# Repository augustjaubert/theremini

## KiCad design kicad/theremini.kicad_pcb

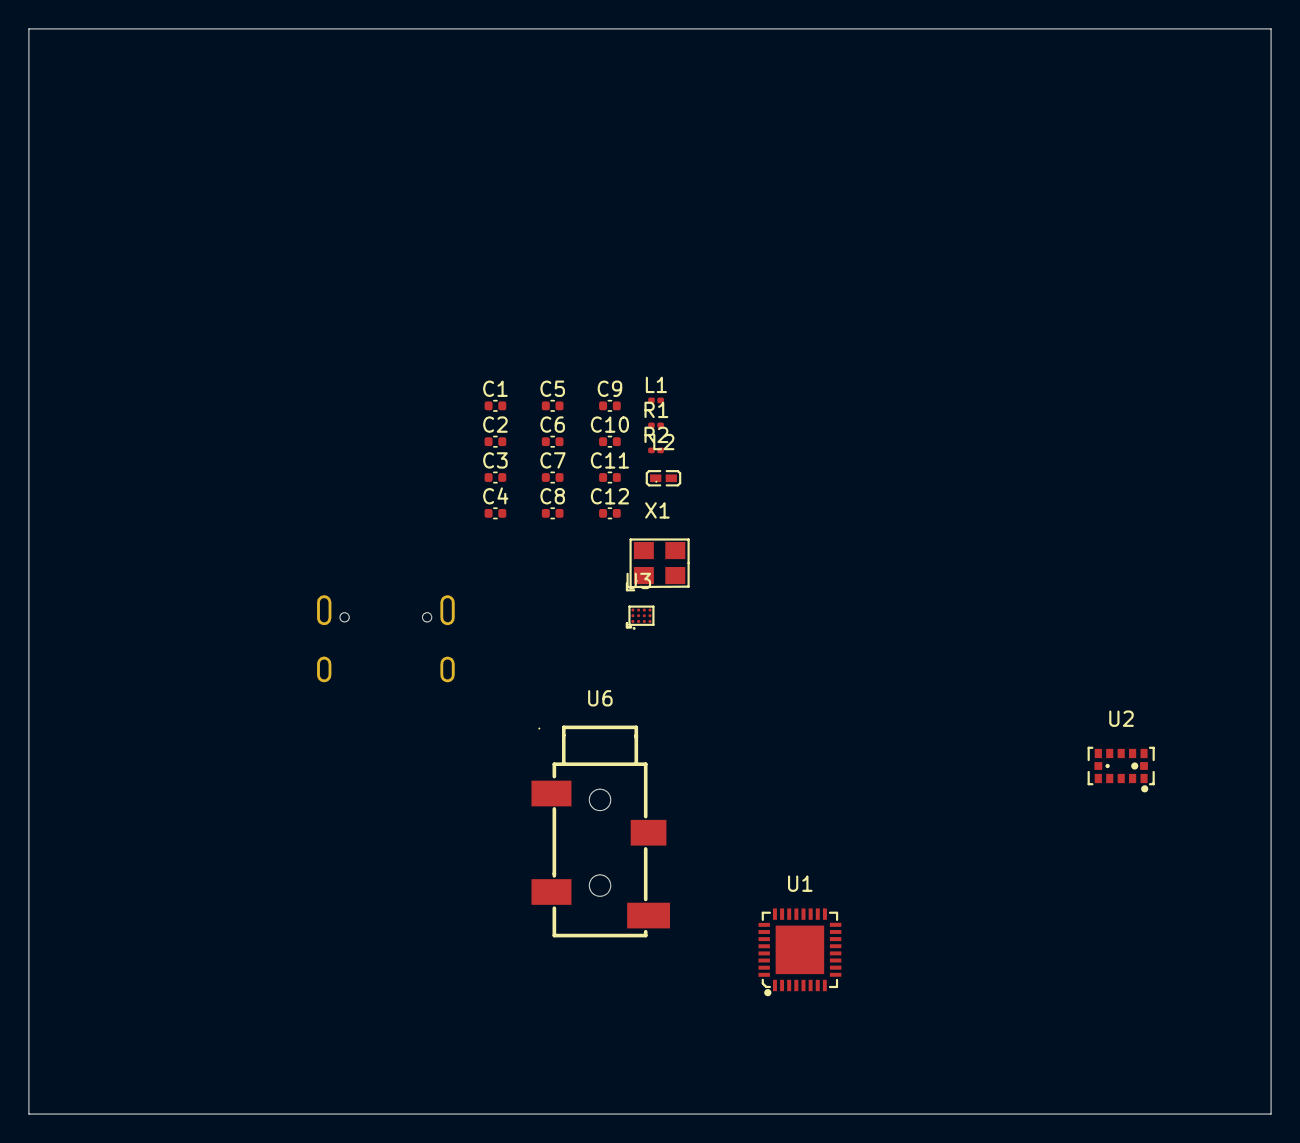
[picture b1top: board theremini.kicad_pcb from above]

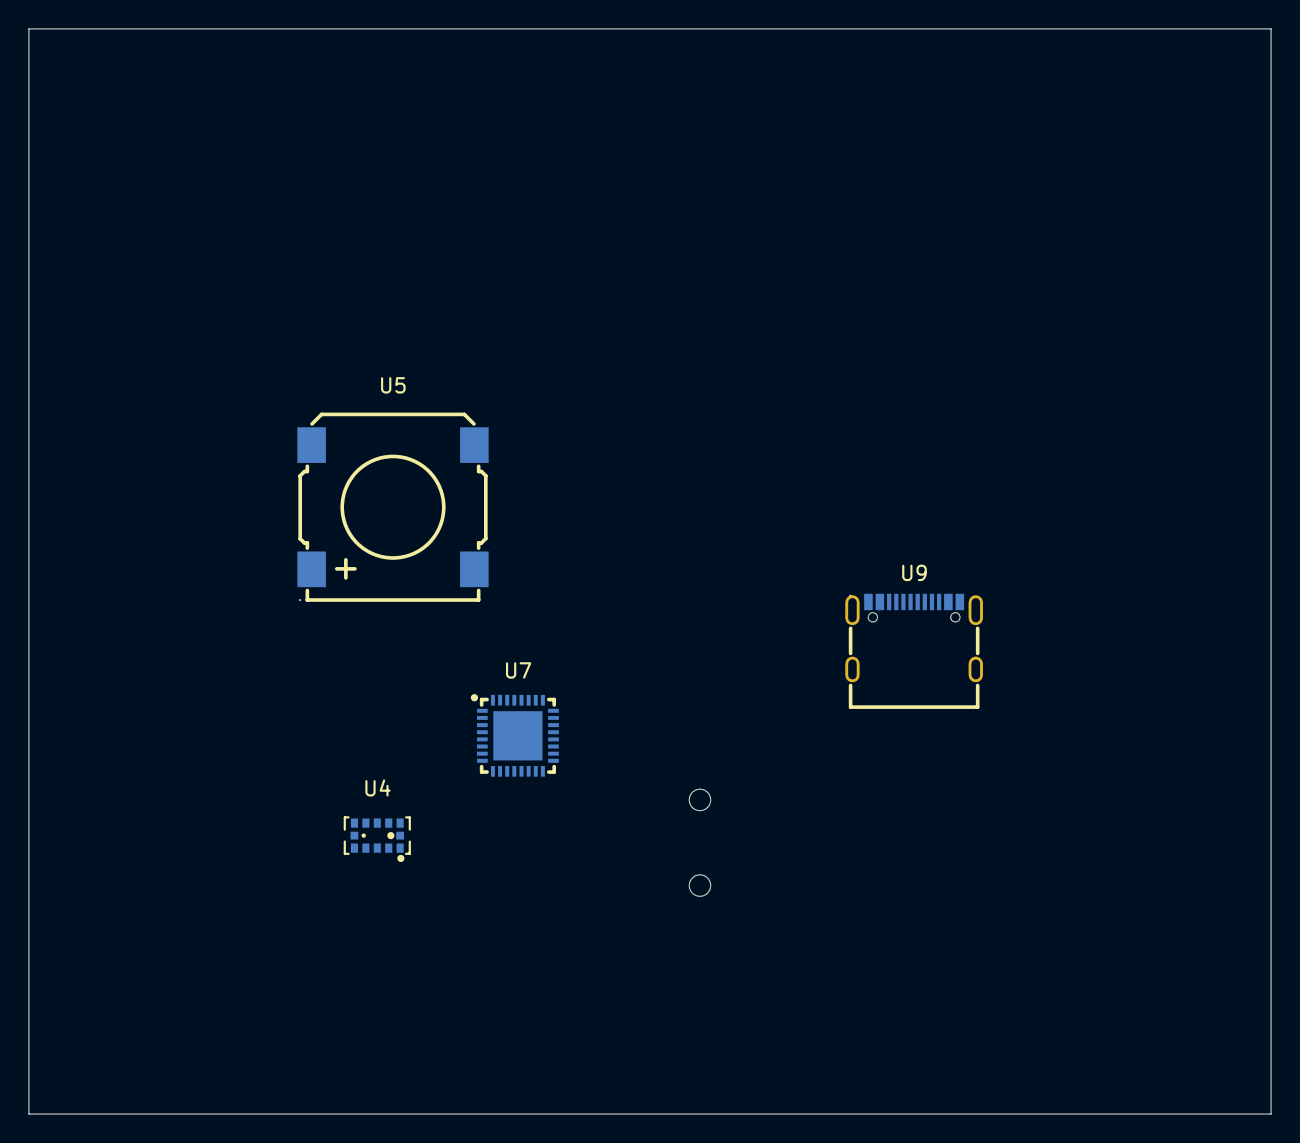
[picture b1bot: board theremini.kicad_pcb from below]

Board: 2 copper layers, 87.0 x 76.0 mm, 25 parts (4 on the bottom side), 12 nets, no tracks yet.

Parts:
C1, C2, C3: 10u; C_0402_1005Metric
C4: 1n; C_0402_1005Metric
C5: 4u7; C_0402_1005Metric
C6, C7, C10, C11: 100n; C_0402_1005Metric
C8: 10n; C_0402_1005Metric
C9: 1u; C_0402_1005Metric
C12: 15p; C_0402_1005Metric
L1: 1.5u; L_0201_0603Metric
L2: BLM15AG601SN1D; L0402
R1: 1M; R_0201_0603Metric
R2: 10k; R_0201_0603Metric
U1: NAU88C22YG; QFN-32_L5.0-W5.0-P0.50-BL-EP3.4
U2, U4: VL53L0CXV0DH/1; OPTO-SMD_12P_VL53L0CXV0DH-1
U3: TPS63051YFFR; DSBGA-12_L1.6-W1.2-R3-C4-P0.40-BL
U5: KLJ-01304T-08R07W; BUZ-SMD_4P-L13.0-W13.0-P11.4-BL
U6: PJ-327C-4A; AUDIO-SMD_PJ-327C-4A
U7: STM32L432KBU6TR; UFQFPN-32_L5.0-W5.0-P0.50-TL-EP3.5
U9: TYPE-C16PIN; USB-C-SMD_TYPE-C16PIN
X1: OT32258MJBA4SL; OSC-SMD_4P-L3.2-W2.5-BL

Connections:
+3.3V: C2.2, C3.2, C5.1, C6.1, C7.1, C11.1, L2.1, R1.2, U3.D1 (VOUT), U3.D2 (FB), U7.1 (VDD), U7.17 (VDD), X1.1 (Tri-state), X1.4 (VDD)
BUCK CONVERTER IN: C1.1, U3.A2 (VIN), U3.A3 (EN), U3.B2 (ILIM0), U3.B3 (ILIM1)
GND: C1.2, C2.1, C3.1, C4.1, C5.2, C6.2, C7.2, C8.2, C9.2, C10.2, C11.2, C12.2, R2.1, U3.B1 (GND), U3.C2 (PFM/PWM), U7.32 (VSS), U9.1 (SHELL), U9.2 (SHELL), U9.3 (SHELL), U9.4 (SHELL), U9.A1B12 (GND), U9.B1A12 (GND), X1.2 (GND)
NRST: C10.1, U7.4 (NRST)
unnamed: U9.A4B9 (VBUS), U9.B4A9 (VBUS)
unnamed: L1.1, U3.A1 (L1)
unnamed: L1.2, U3.C1 (L2)
unnamed: R1.1, U3.C3 (PG)
unnamed: C4.2, U3.D3 (SS)
unnamed: R2.2, U7.31 (PH3/BOOT0)
VDDA: C8.1, C9.1, L2.2, U7.5 (VDDA/VREF+)
XTAL OUT: C12.1, U7.6 (PA0/CK_IN), X1.3 (OUTPUT)

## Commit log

2024-12-04 init commit
2024-12-04 move files around
2024-12-04 added libraries
2024-12-04 Add libraries
2024-12-04 Place footprints
2024-12-05 move backup folder
2024-12-05 added things
2024-12-12 Arrange library
2024-12-13 New libs
2024-12-14 Connected things
2024-12-15 just update ig
2024-12-16 just commit
2024-12-20 quick quick quiiick
